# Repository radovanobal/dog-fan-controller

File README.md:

# Dog Fan Controller

A PWM controller for two Noctua NF-A14 PWM fans, using an ESP32-C3 SuperMini
and an external SHT4x temperature and humidity sensor.

## Licence and attribution

Copyright © 2026 **Appicanis, Radovan Obal s.p.**

The original hardware design and accompanying design documentation are
licensed under **CERN-OHL-P-2.0**. See [LICENSE](LICENSE) for the complete
licence and [NOTICE](NOTICE) for attribution, source location and scope.

You may use, modify, manufacture and sell the design, including commercially.
You do not have to publish your modifications. When redistributing design
materials, retain the applicable notices and provide the licence; when
redistributing modified design materials, also identify and date your changes.
When supplying physical products, ensure recipients can access the applicable
notices, as required by section 4 of the licence. We impose no additional
requirement for prominent branding or credit on a product or sales page.

Original design: **Appicanis, Radovan Obal s.p.**  
Source: <https://github.com/radovanobal/dog-fan-controller>

Third-party materials retain their own licences. Firmware and standalone
software require their own explicit licence; the hardware licence above
does not automatically apply to them.

## Open on another machine

Install **KiCad 10** with its standard symbol, footprint and 3D model libraries,
clone this repository, then open `Fan Controller.kicad_pro` in KiCad.
No personal library configuration or custom path variables are required.

The project library tables explicitly reference KiCad's standard libraries using
`KICAD10_SYMBOL_DIR` and `KICAD10_FOOTPRINT_DIR`. Custom dependencies are included
in `custom_footprints.pretty/`, `Fan_Controller.pretty/`, `symbols/` and
`3dmodels/`, and use `${KIPRJMOD}` paths relative to the checkout. The two
root-level symbol libraries are also registered in the project table. Standard
3D models use KiCad's `KICAD10_3DMODEL_DIR` setting.

When adding a custom part, include its symbol, footprint and any 3D model in the
repository and update the project library tables. Avoid absolute paths or
libraries registered only in your personal KiCad settings.

## Manufacturing preparation

JLCPCB fabrication and draft assembly outputs, order settings and review status
are in [manufacturing/jlcpcb](manufacturing/jlcpcb/README.md). Regenerate exports
with `python3 tools/prepare_jlcpcb.py` using KiCad 10.

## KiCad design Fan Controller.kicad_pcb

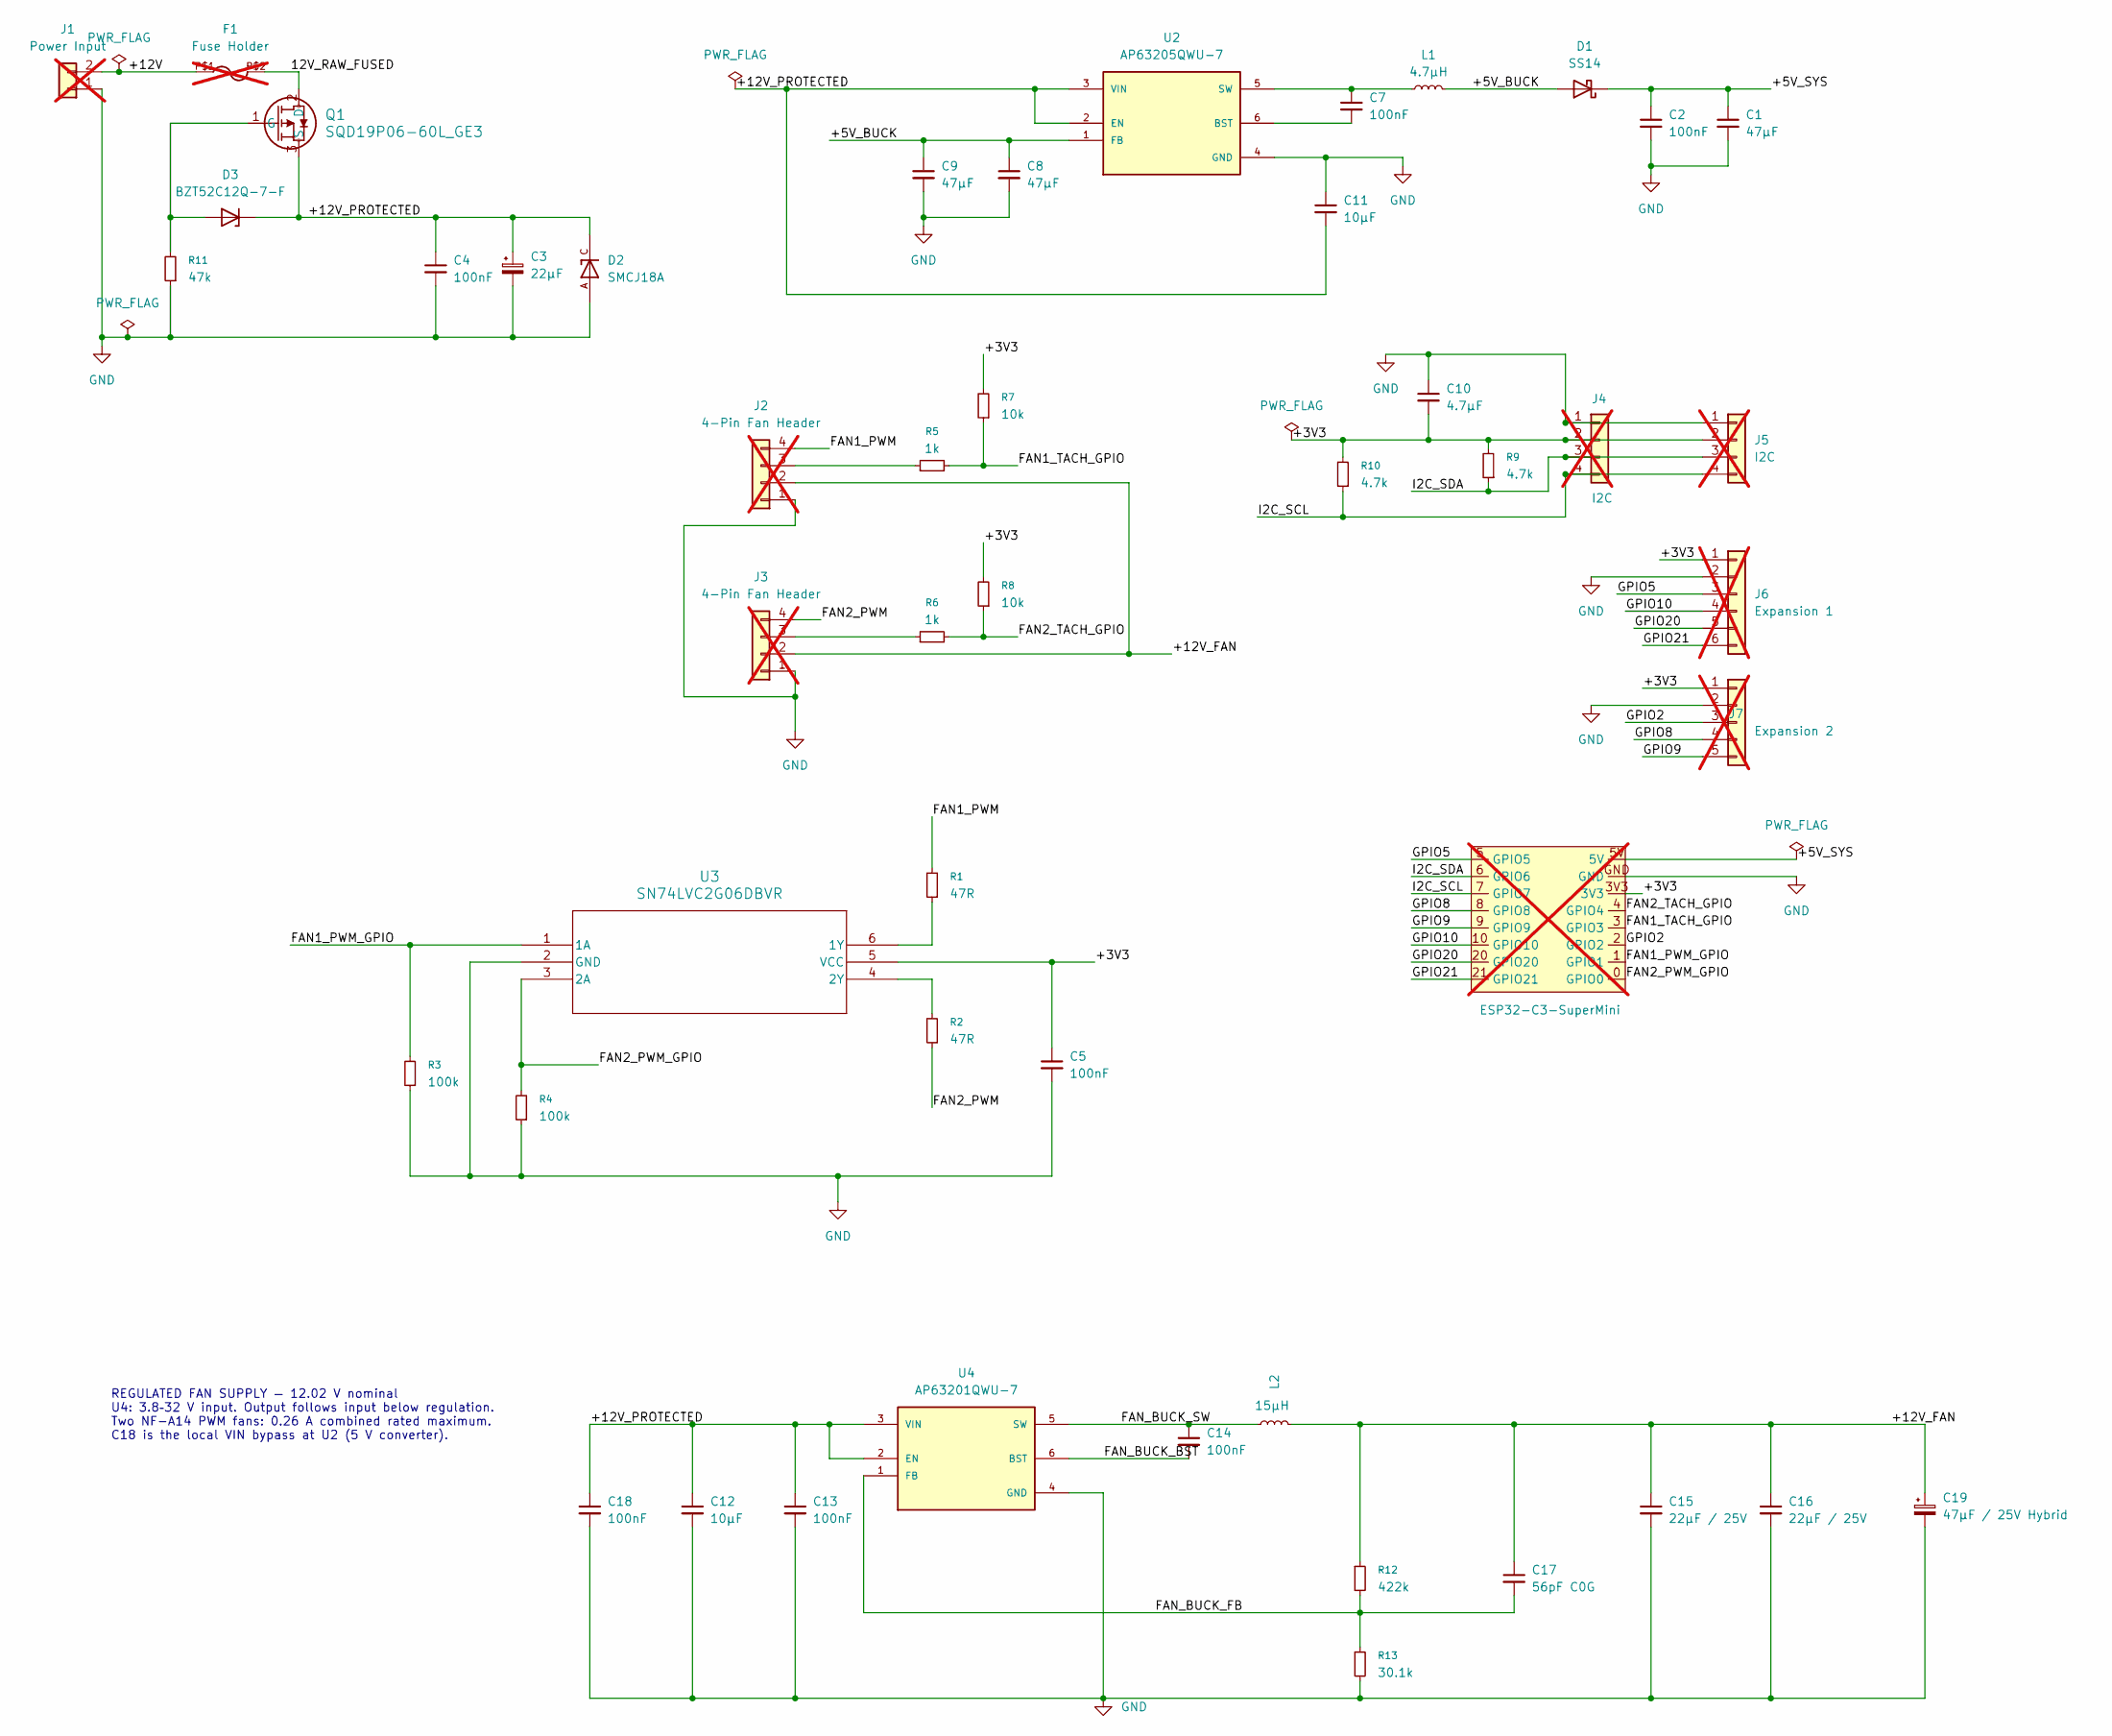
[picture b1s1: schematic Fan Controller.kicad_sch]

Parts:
C1, C8, C9: 47µF; C_1210_3225Metric; MPN GRM32ER71A476KE15L; LCSC C84494
C2, C4, C5, C13, C18: 100nF; C_0805_2012Metric; MPN CL21B104KBCNNNC; LCSC C1711
C3: 22µF; CP_Elec_6.3x5.8; MPN EEEHB1V220P; LCSC C336302
C7, C14: 100nF; C_0603_1608Metric; MPN CL10B104KB8NNNC; LCSC C1591
C10: 4.7µF; C_0805_2012Metric; MPN GRM21BR71C475KA73L; LCSC C86040
C11, C12: 10µF; C_1206_3216Metric; MPN CL31B106KBHNNNE; LCSC C89632
C15, C16: 22µF / 25V; C_1210_3225Metric; MPN C1210C226M3RAC7800; LCSC C3852592
C17: 56pF C0G; C_0805_2012Metric; MPN C0805C560G1GACTU; LCSC C2277731
C19: 47µF / 25V Hybrid; CP_Elec_6.3x5.8; MPN EEHZC1E470P; LCSC C542308
D1: SS14; D_SMA; MPN SS14-E3/61T; LCSC C47460
D2: SMCJ18A; DIOM7959X262N; PARTREV 11/20/15; LCSC C374030
D3: BZT52C12Q-7-F; D_SOD-123; MPN BZT52C12Q-7-F; LCSC C460785
F1: Fuse Holder; LITTLEFUSE_178.6764.0001; MPN 178.6764.0001; not fitted
J1: Power Input; JST_XH_B2B-XH-A_1x02_P2.50mm_Vertical; MPN B2B-XH-A (LF) (SN); LCSC C158012; not fitted
J2, J3: 4-Pin Fan Header; CONN_SD-47053-001_H10P00_MOL; MPN 470531000; LCSC C240840; not fitted
J4, J5: I2C; JST_PH_B4B-PH-K_1x04_P2.00mm_Vertical; MPN B4B-PH-K-S (LF) (SN); LCSC C131334; not fitted
J6: Expansion 1; JST_PH_B6B-PH-K_1x06_P2.00mm_Vertical; MPN B6B-PH-K-S (LF) (SN); LCSC C131342; not fitted
J7: Expansion 2; JST_PH_B5B-PH-K_1x05_P2.00mm_Vertical; MPN B5B-PH-K-S (LF) (SN); LCSC C157993; not fitted
L1: 4.7µH; IND_SPM5030T-4R7M-HZ; MPN SPM5030T-4R7M-HZ; LCSC C435271
L2: 15µH; IND_SPM6530T-150M-HZ; MPN SPM6530T-150M-HZ; LCSC C307809
Q1: SQD19P06-60L_GE3; TO252AA_SQD19_VIS; MPN SQD19P06-60L_GE3; LCSC C143665
R1, R2: 47R; R_0805_2012Metric; MPN RC0805FR-0747RL; LCSC C114541
R3, R4: 100k; R_0805_2012Metric; MPN RC0805FR-07100KL; LCSC C96346
R5, R6: 1k; R_0805_2012Metric; MPN RC0805FR-071KL; LCSC C95781
R7, R8: 10k; R_0805_2012Metric; MPN RC0805FR-0710KL; LCSC C84376
R9, R10: 4.7k; R_0805_2012Metric; MPN RC0805FR-074K7L; LCSC C60816
R11: 47k; R_0805_2012Metric; MPN RC0805FR-0747KL; LCSC C126351
R12: 422k; R_0805_2012Metric; MPN RC0805FR-07422KL; LCSC C273967
R13: 30.1k; R_0805_2012Metric; MPN RC0805FR-0730K1L; LCSC C163407
U1: ESP32-C3-SuperMini; MPN ESP32-C3-SuperMini; not fitted
U2: AP63205QWU-7; SOT95P280X100-6N; PARTREV 1 - 2; LCSC C5248537
U3: SN74LVC2G06DBVR; SOT-23-6; MPN SN74LVC2G06DBVR; LCSC C402162
U4: AP63201QWU-7; SOT95P280X100-6N; PARTREV 1 - 2; LCSC C5248535

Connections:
/12V_RAW_FUSED: F1.P$2, Q1.2 (D)
/+3V3: C5.1, C10.2, J4.2, J5.2, J6.1, J7.1, R7.2, R8.2, R9.2, R10.2, U1.3V3, U3.5 (VCC)
/+5V_BUCK: C8.1, C9.1, D1.2 (A), L1.2, U2.1 (FB)
/+5V_SYS: C1.1, C2.1, D1.1 (K), U1.5V
/+12V: F1.P$1, J1.2
/+12V_FAN: C15.1, C16.1, C17.1, C19.1, J2.2, J3.2, L2.2, R12.1
/+12V_PROTECTED: C3.1, C4.1, C11.2, C12.1, C13.1, C18.1, D2.C, D3.1 (K), Q1.3 (S), U2.2 (EN), U2.3 (VIN), U4.2 (EN), U4.3 (VIN)
/FAN1_PWM: J2.4, R1.2
/FAN1_PWM_GPIO: R3.2, U1.1 (GPIO1), U3.1 (1A)
/FAN1_TACH_GPIO: R5.2, R7.1, U1.3 (GPIO3)
/FAN2_PWM: J3.4, R2.1
/FAN2_PWM_GPIO: R4.2, U1.0 (GPIO0), U3.3 (2A)
/FAN2_TACH_GPIO: R6.2, R8.1, U1.4 (GPIO4)
/FAN_BUCK_BST: C14.2, U4.6 (BST)
/FAN_BUCK_FB: C17.2, R12.2, R13.1, U4.1 (FB)
/FAN_BUCK_SW: C14.1, L2.1, U4.5 (SW)
/GPIO2: J7.3, U1.2 (GPIO2)
/GPIO5: J6.3, U1.5 (GPIO5)
/GPIO8: J7.4, U1.8 (GPIO8)
/GPIO9: J7.5, U1.9 (GPIO9)
/GPIO10: J6.4, U1.10 (GPIO10)
/GPIO20: J6.5, U1.20 (GPIO20)
/GPIO21: J6.6, U1.21 (GPIO21)
/I2C_SCL: J4.4, J5.4, R10.1, U1.7 (GPIO7)
/I2C_SDA: J4.3, J5.3, R9.1, U1.6 (GPIO6)
GND: C1.2, C2.2, C3.2, C4.2, C5.2, C8.2, C9.2, C10.1, C11.1, C12.2, C13.2, C15.2, C16.2, C18.2, C19.2, D2.A, J1.1, J2.1, J3.1, J4.1, J5.1, J6.2, J7.2, R3.1, R4.1, R11.1, R13.2, U1.GND, U2.4 (GND), U3.2 (GND), U4.4 (GND)
unnamed: D3.2 (A), Q1.1 (G), R11.2
unnamed: J2.3, R5.1
unnamed: J3.3, R6.1
unnamed: C7.2, U2.6 (BST)
unnamed: C7.1, L1.1, U2.5 (SW)
unnamed: R1.1, U3.6 (1Y)
unnamed: R2.2, U3.4 (2Y)

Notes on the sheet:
REGULATED FAN SUPPLY — 12.02 V nominal U4: 3.8–32 V input. Output follows input below regulation. Two NF-A14 PWM fans: 0.26 A combined rated maximum. C18 is the local VIN bypass at U2 (5 V converter).

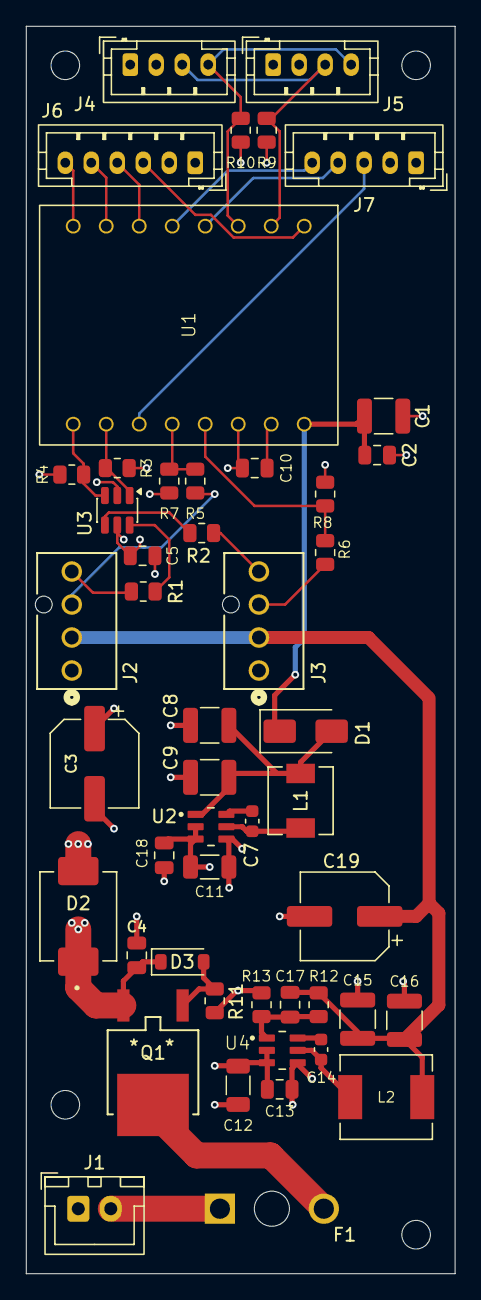
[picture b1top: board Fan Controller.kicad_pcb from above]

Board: 4 copper layers, 33.0 x 96.0 mm, 53 parts (0 on the bottom side), 33 nets.

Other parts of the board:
H1, H2, H3, H4: MountingHole_2.2mm_M2

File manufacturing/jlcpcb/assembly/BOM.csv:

Comment,Designator,Footprint,LCSC Part #,Manufacturer Part Number,Manufacturer,Quantity
47µF,"C1,C8,C9",C_1210_3225Metric,C84494,GRM32ER71A476KE15L,Murata,3
100nF,"C2,C4,C5,C13,C18",C_0805_2012Metric,C1711,CL21B104KBCNNNC,Samsung Electro-Mechanics,5
22µF,C3,CP_Elec_6.3x5.8,C336302,EEEHB1V220P,Panasonic,1
100nF,"C7,C14",C_0603_1608Metric,C1591,CL10B104KB8NNNC,Samsung Electro-Mechanics,2
4.7µF,C10,C_0805_2012Metric,C86040,GRM21BR71C475KA73L,Murata,1
10µF,"C11,C12",C_1206_3216Metric,C89632,CL31B106KBHNNNE,Samsung Electro-Mechanics,2
22µF / 25V,"C15,C16",C_1210_3225Metric,C3852592,C1210C226M3RAC7800,KEMET,2
56pF C0G,C17,C_0805_2012Metric,C2277731,C0805C560G1GACTU,KEMET,1
47µF / 25V Hybrid,C19,CP_Elec_6.3x5.8,C542308,EEHZC1E470P,Panasonic,1
SS14,D1,D_SMA,C47460,SS14-E3/61T,Vishay,1
SMCJ18A,D2,DIOM7959X262N,C374030,SMCJ18A,Littelfuse,1
BZT52C12Q-7-F,D3,D_SOD-123,C460785,BZT52C12Q-7-F,Diodes Inc.,1
4.7µH,L1,IND_SPM5030T-4R7M-HZ,C435271,SPM5030T-4R7M-HZ,TDK,1
15µH,L2,IND_SPM6530T-150M-HZ,C307809,SPM6530T-150M-HZ,TDK,1
SQD19P06-60L_GE3,Q1,TO252AA_SQD19_VIS,C143665,SQD19P06-60L_GE3,Vishay,1
47R,"R1,R2",R_0805_2012Metric,C114541,RC0805FR-0747RL,Yageo,2
100k,"R3,R4",R_0805_2012Metric,C96346,RC0805FR-07100KL,Yageo,2
1k,"R5,R6",R_0805_2012Metric,C95781,RC0805FR-071KL,Yageo,2
10k,"R7,R8",R_0805_2012Metric,C84376,RC0805FR-0710KL,Yageo,2
4.7k,"R9,R10",R_0805_2012Metric,C60816,RC0805FR-074K7L,Yageo,2
47k,R11,R_0805_2012Metric,C126351,RC0805FR-0747KL,Yageo,1
422k,R12,R_0805_2012Metric,C273967,RC0805FR-07422KL,Yageo,1
30.1k,R13,R_0805_2012Metric,C163407,RC0805FR-0730K1L,Yageo,1
AP63205QWU-7,U2,SOT95P280X100-6N,C5248537,AP63205QWU-7,Diodes Inc.,1
SN74LVC2G06DBVR,U3,SOT-23-6,C402162,SN74LVC2G06DBVR,Texas Instruments,1
AP63201QWU-7,U4,SOT95P280X100-6N,C5248535,AP63201QWU-7,Diodes Inc.,1
